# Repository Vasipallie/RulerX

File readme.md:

# RulerX

RulerX is a smart ruler which also acts as an NFC tag, allowing you to share you favourite websites and contact details with just a tap. This ruler has been designed with the intention of being given as a momento to the team at the GIIS Robotics Club.

View the demo at [user-cdn.hackclub-assets.com/019f37bf-e643-794e-a864-747f67c8363c/e4663d0b-7505-419f-bef5-393dbbf44ca0.MP4](https://user-cdn.hackclub-assets.com/019f37bf-e643-794e-a864-747f67c8363c/e4663d0b-7505-419f-bef5-393dbbf44ca0.MP4)

# Important Links

- [RulerX/production/BOM.csv at main · Vasipallie/RulerX](https://github.com/Vasipallie/RulerX/blob/main/production/BOM.csv) BOM.CSV file
-

# Bill of Materials

| Comment            | Designator | Footprint                                | JLCPCB Part # | Price (USD) |
| ------------------ | ---------- | ---------------------------------------- | ------------- | ----------: |
| NFC BUSINESS       | ANT1       | NFC ANTENNA                              | —             |           — |
| 220nF              | C1         | C0603                                    | C64705        |      $0.010 |
| 47Ω                | R1         | R1206                                    | C2889662      |      $0.003 |
| NT3H2111W0FHKH     | U1         | XQFN-8_L1.6-W1.6-P0.50-BL_NT3H2111W0FHKH | C710403       |      $0.808 |
| 19-21/GHC-YR1S2/4T | U2         | LED0603-R-RD                             | C2986048      |      $0.026 |
| **TOTAL**          |            |                                          |               |  **$0.847** |

# Schematic and PCB

## Notes:

All schematic and PCB files have been provided in the source folder. These can be modified accordingly to suit your personal needs.

Production files have been provided under the production folder, this can be used to manufacture an exact replica of the NFC ruler.

Production folder:

1. BOM.xlsx (Bill of materials in XLSX format)
2. grburger.zip (Gerber files for machining)
3. PCLK.csv (Pick and Place file)

Please note that these production files have been made specifically for JLCPCB (which is what I am using for PCB manufacturing), you may need to adjust them accordingly for other PCB manufacturers (Please see their requirements on their website).

# Contribution

If you feel like there should be other features embedded into this PCB Ruler, you are free to make changes and open a pull request. I will review them and approve accordingly

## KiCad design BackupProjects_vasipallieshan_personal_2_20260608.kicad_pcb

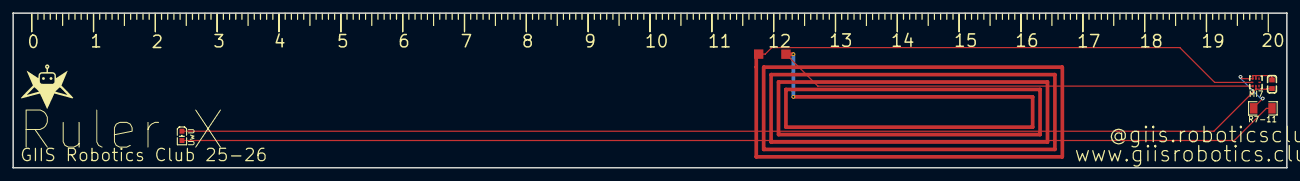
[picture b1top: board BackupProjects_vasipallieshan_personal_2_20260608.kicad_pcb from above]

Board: 2 copper layers, 206.0 x 25.0 mm, 6 parts (0 on the bottom side), 5 nets.

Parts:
ANT1: NFC BUSINESS; NFC ANTENNA
C1: 220nF; C0603
R7-11: 47Ω; R1206
U1: NT3H2111W0FHKH; XQFN-8_L1.6-W1.6-P0.50-BL_NT3H2111W0FHKH
UwU: 19-21/GHC-YR1S2/4T; LED0603-R-RD
i: LOGO; dun

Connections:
U1_1: ANT1.2, U1.1
U1_2: C1.1, U1.2, UwU.2
U1_6: C1.2, R7-11.2, U1.6, U1.7
U1_8: ANT1.1, U1.8
U2_1: R7-11.1, UwU.1

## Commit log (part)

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2026-06-10 added files forreiview
2026-06-10 added readme
2026-06-10 syntax change
2026-06-10 added images
2026-06-15 Formatted repo for ease of access
2026-06-25 updates according to guidelines
